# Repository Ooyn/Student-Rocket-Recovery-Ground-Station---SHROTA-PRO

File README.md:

# Student-Rocket-Recovery-Ground-Station---SHROTA-PRO
Shrota Pro is a custom-engineered, portable ground station PCB specifically designed to track and recover student-built rockets after touchdown. Acting as a specialized, relative GPS system, the handheld device receives critical telemetry data from the rocket and calculates its exact landing coordinates relative to the user's current position, making post-flight retrieval highly efficient.

At the heart of the system is an STM32 microcontroller responsible for real-time processing of incoming telemetry, parsing GPS data, managing sensor inputs, and driving the user interface. The board is powered by a 7.4V dual battery bus, utilizing step-down switching regulators to provide stable 5V and 3.3V rails. This robust power management ensures reliable operation of the MCU, sensitive RF equipment, and the onboard screen interface, allowing users to read relative distances and headings directly in the field. Standardized USB connectivity is also integrated for flashing firmware and serial debugging.

To accurately pinpoint positions, the board utilizes a multi-sensor navigation suite featuring an L89 GNSS module, a NEO-M8N GNSS module, and a BMM150 3-axis geomagnetic sensor that acts as a digital compass to determine the user's precise heading. For reliable long-range telemetry reception, the system incorporates a versatile radio block. It integrates RYLR998 and LLCC68 LoRa modules for robust, low-power communication links, alongside an RFD900x radio modem interface for extended range, ensuring the recovery team maintains a solid, line-of-sight connection to the downed rocket.

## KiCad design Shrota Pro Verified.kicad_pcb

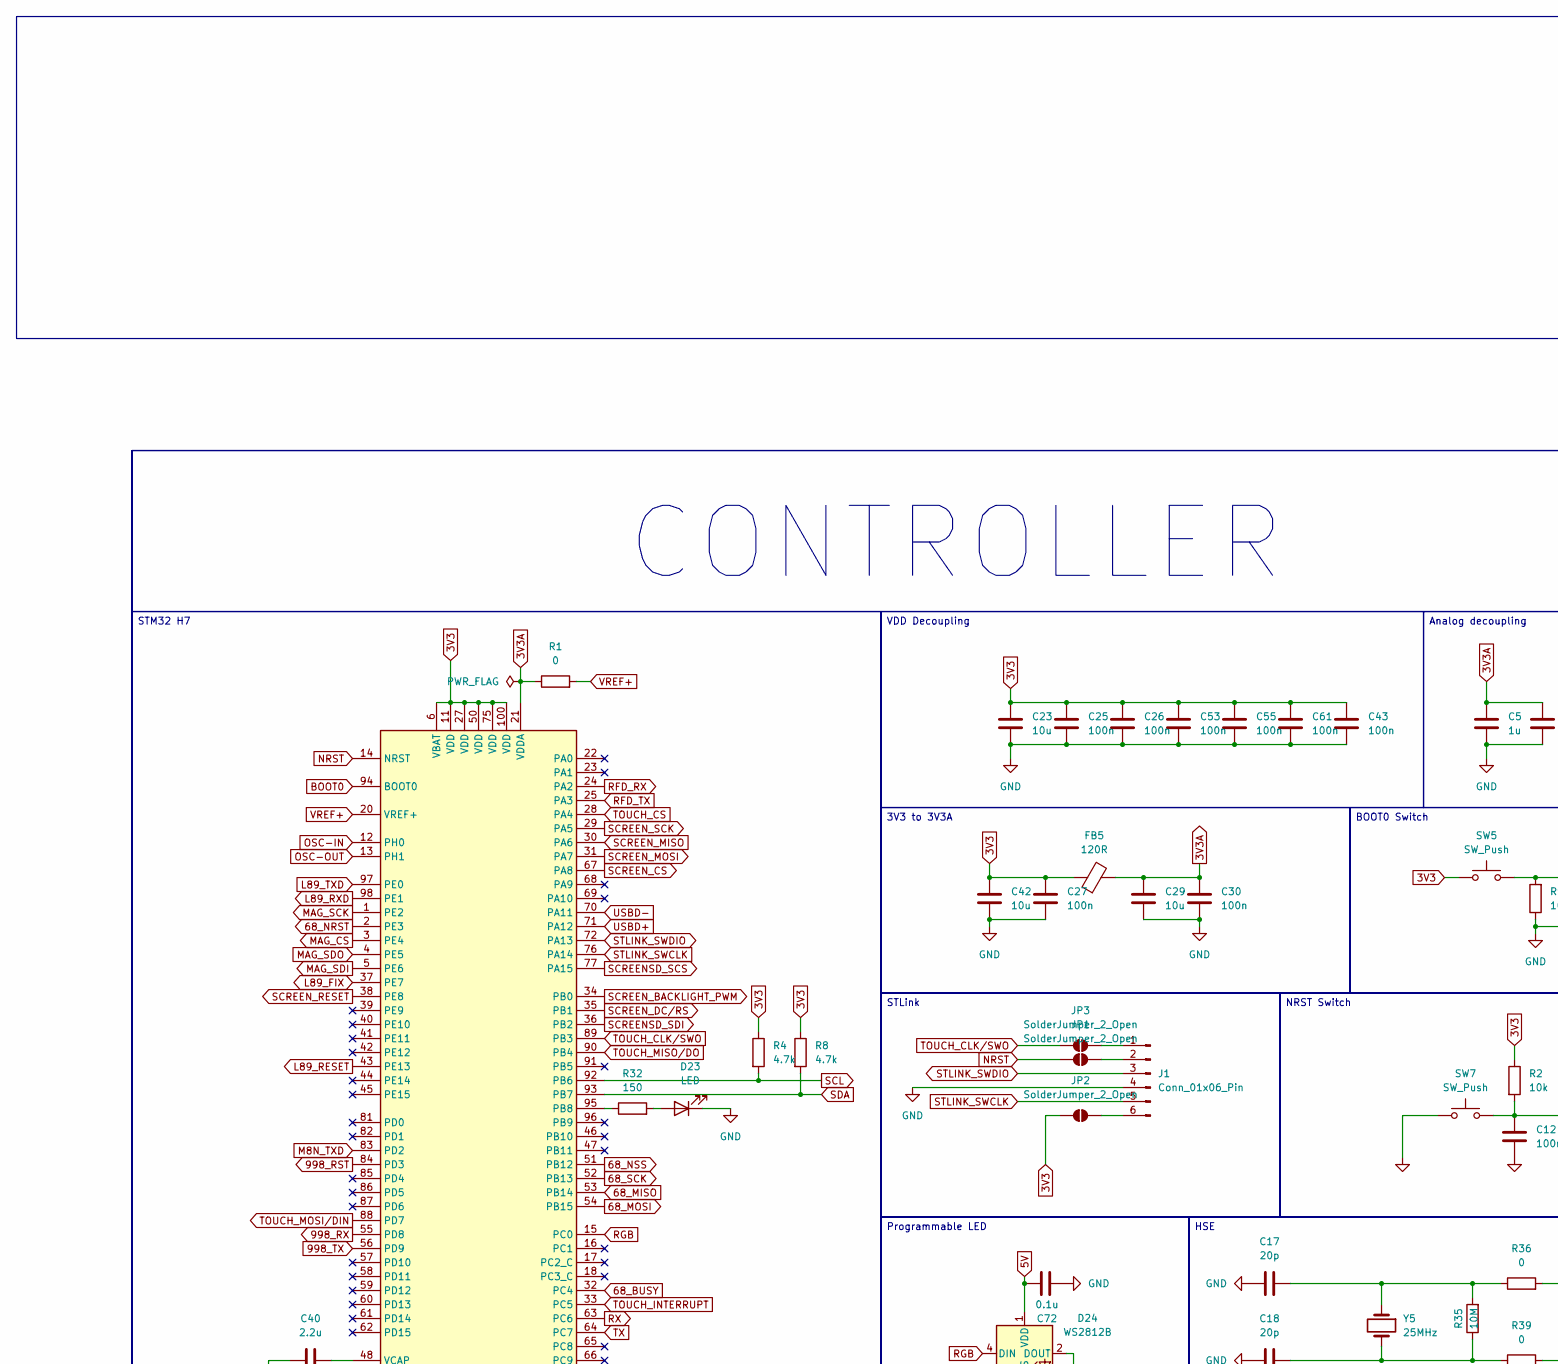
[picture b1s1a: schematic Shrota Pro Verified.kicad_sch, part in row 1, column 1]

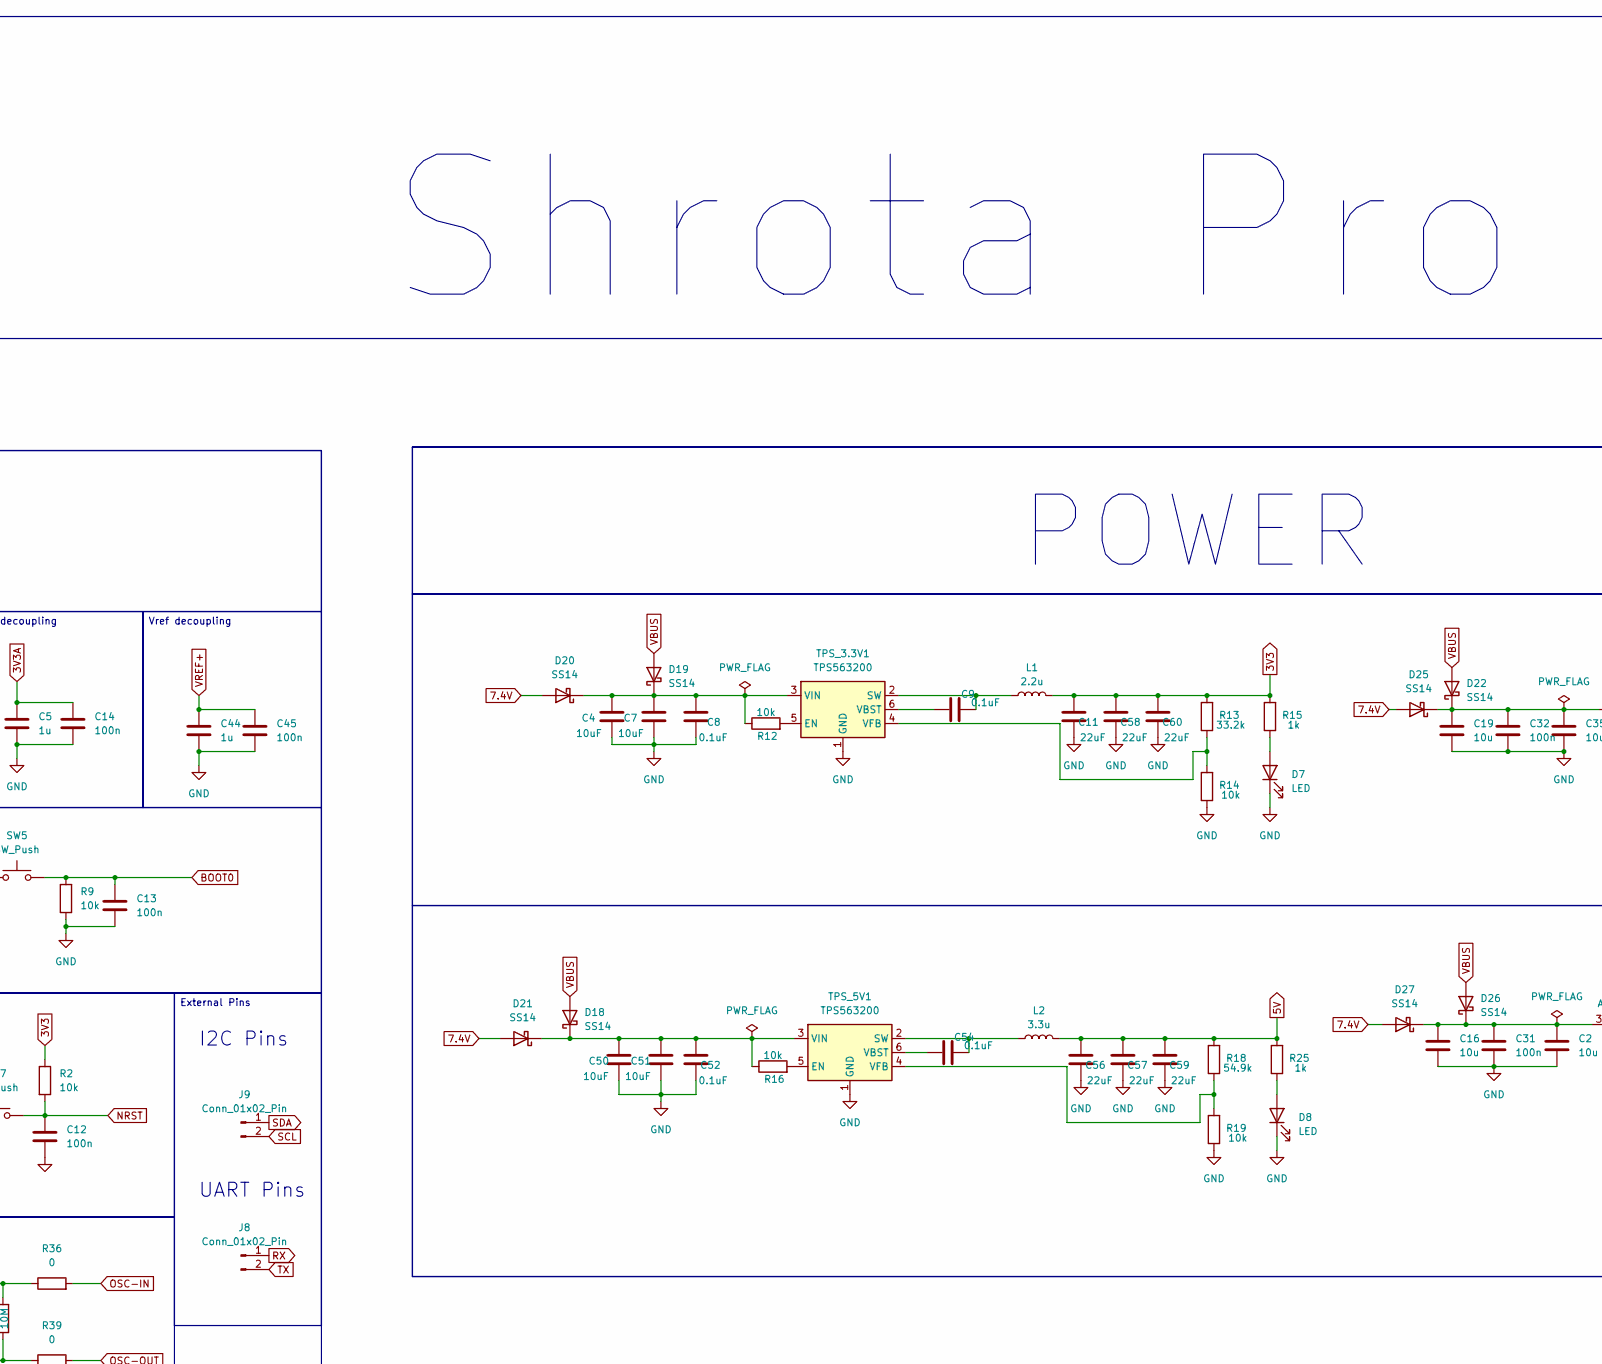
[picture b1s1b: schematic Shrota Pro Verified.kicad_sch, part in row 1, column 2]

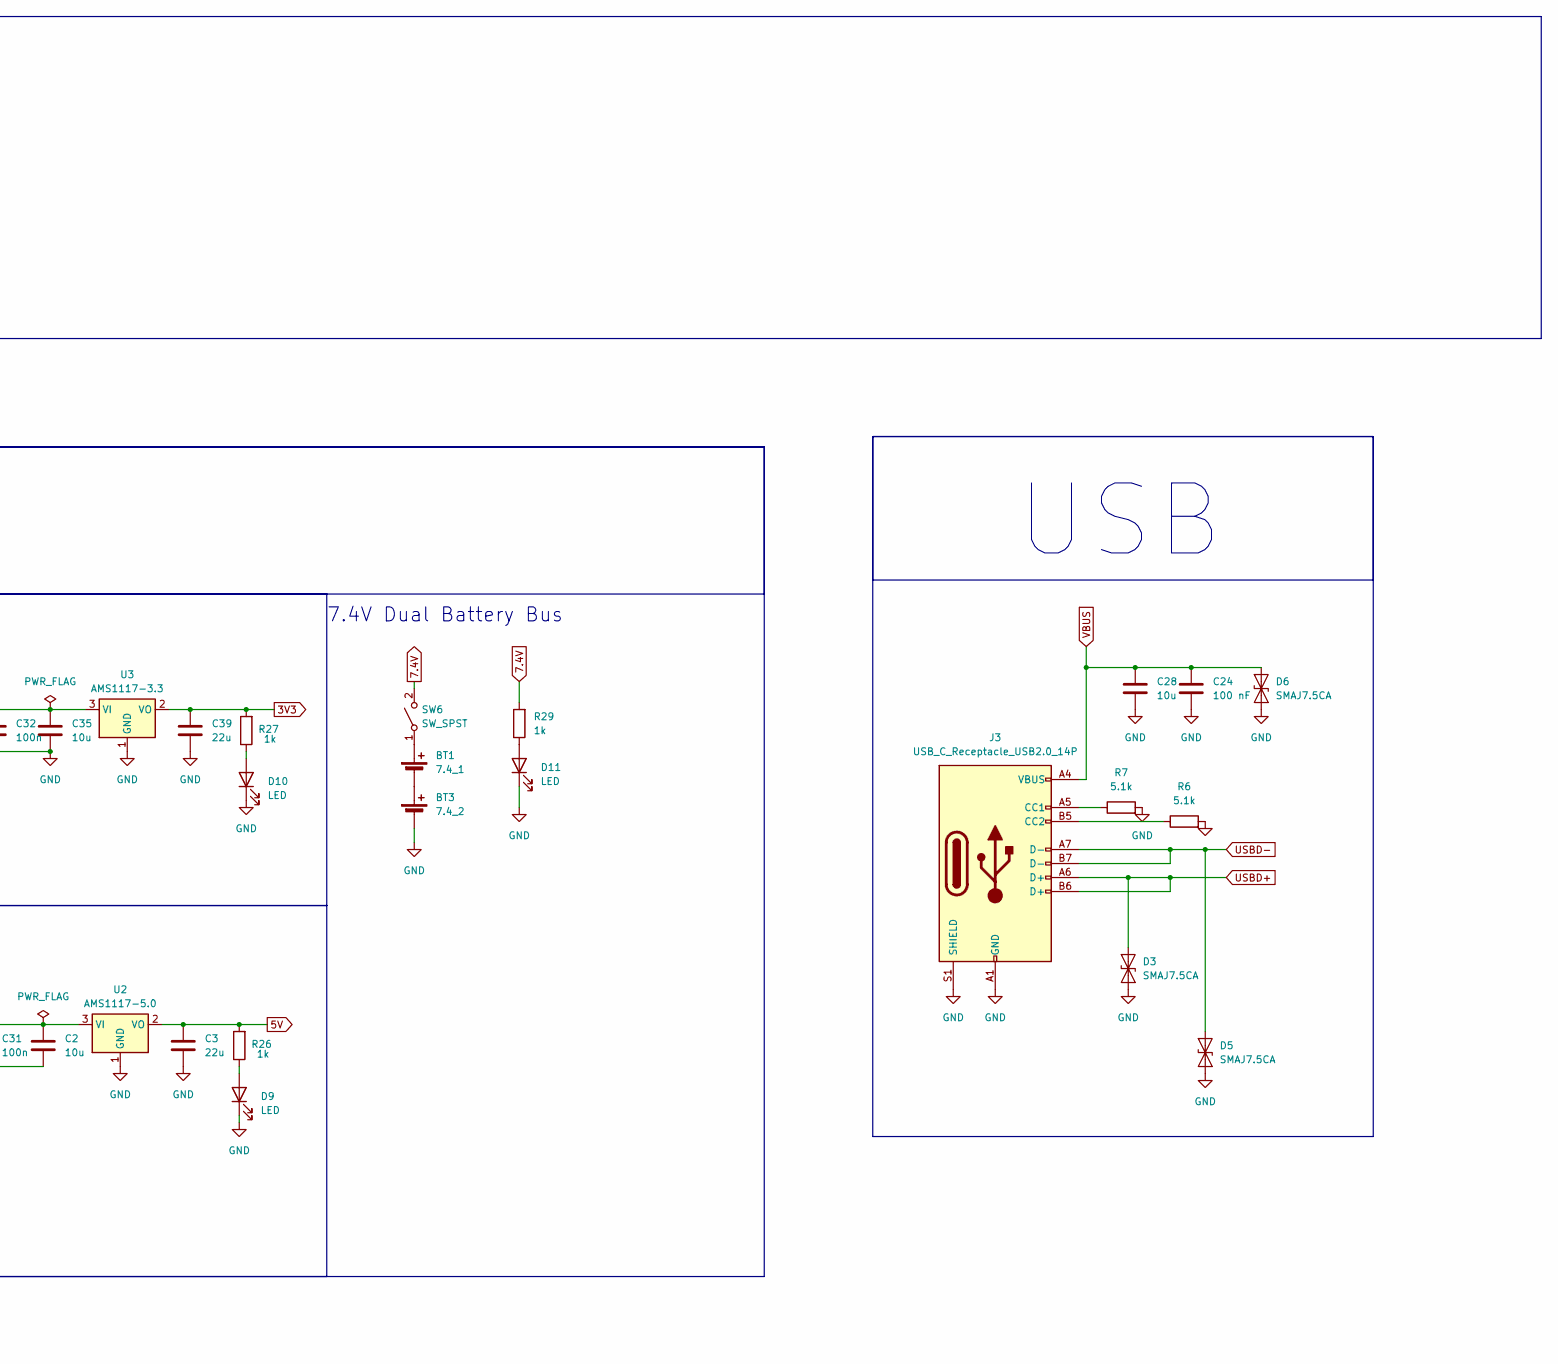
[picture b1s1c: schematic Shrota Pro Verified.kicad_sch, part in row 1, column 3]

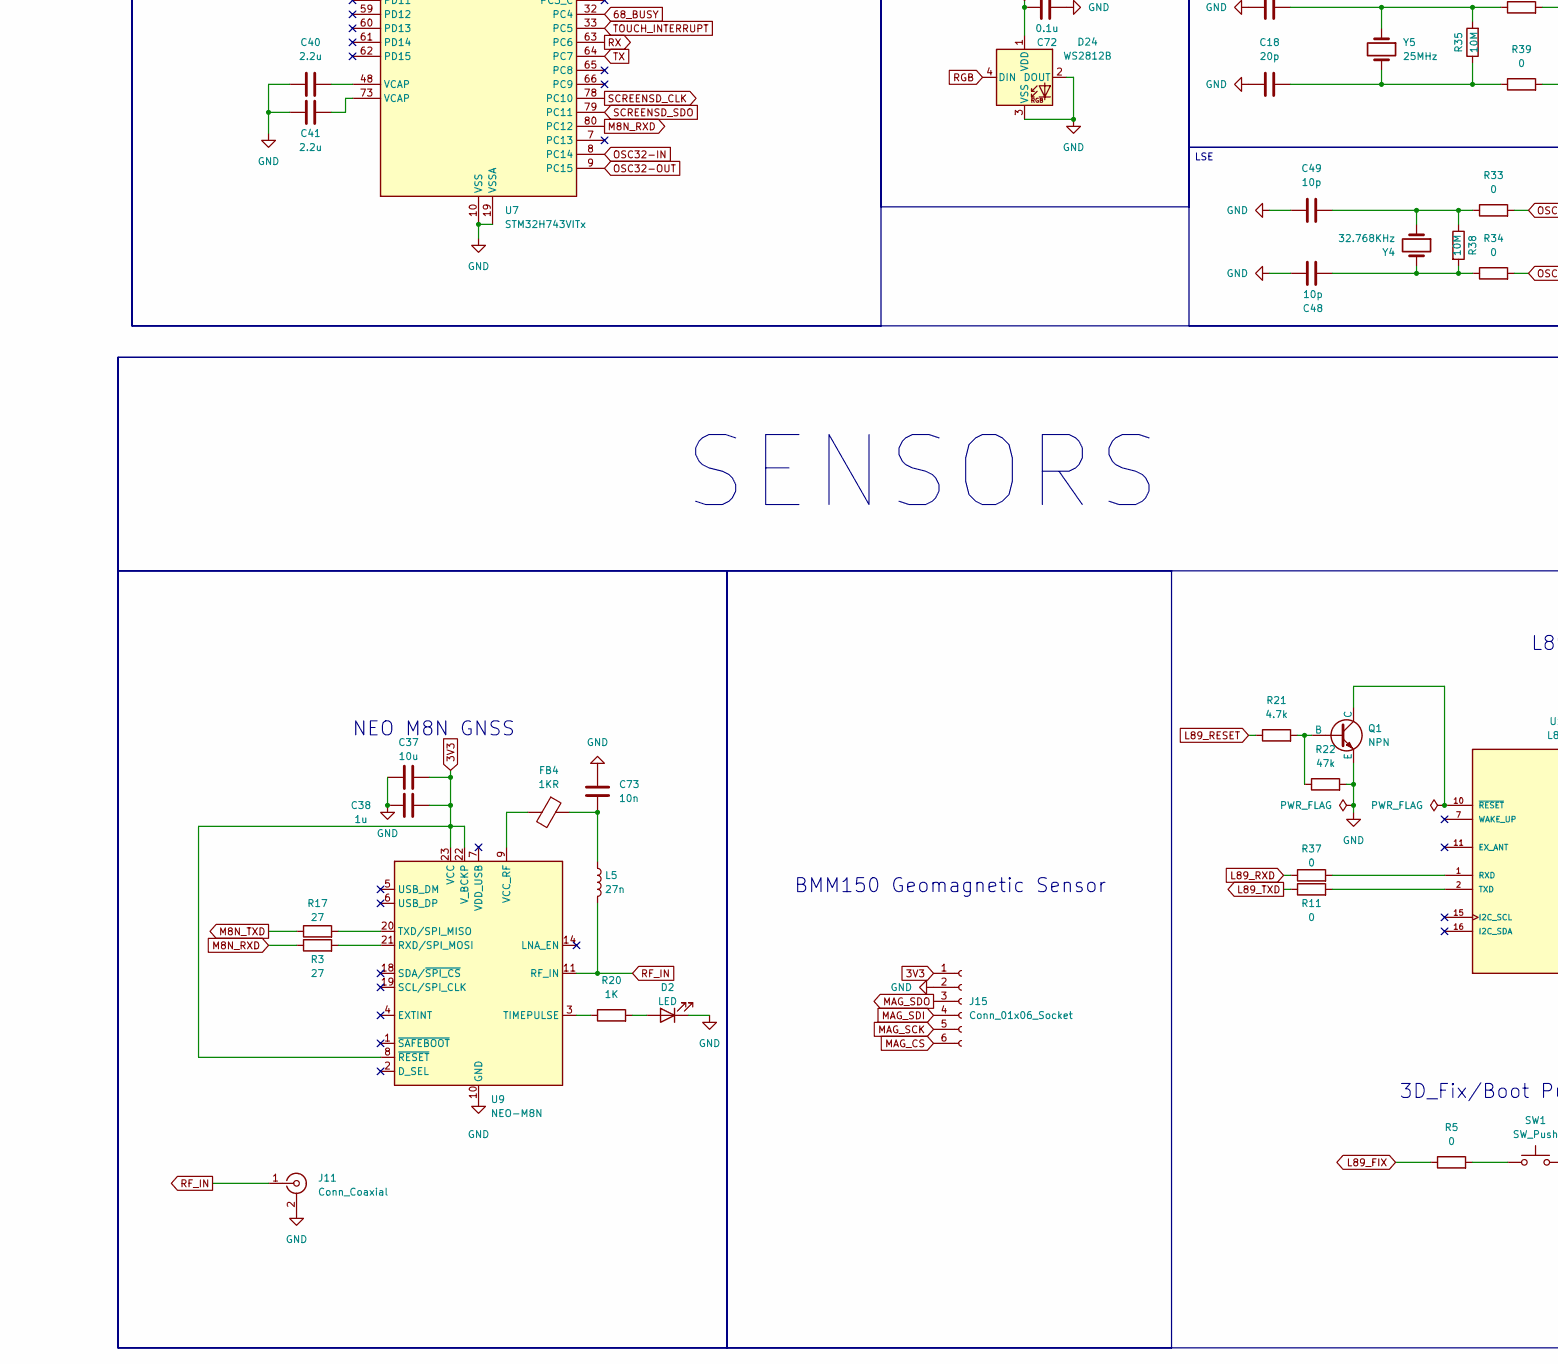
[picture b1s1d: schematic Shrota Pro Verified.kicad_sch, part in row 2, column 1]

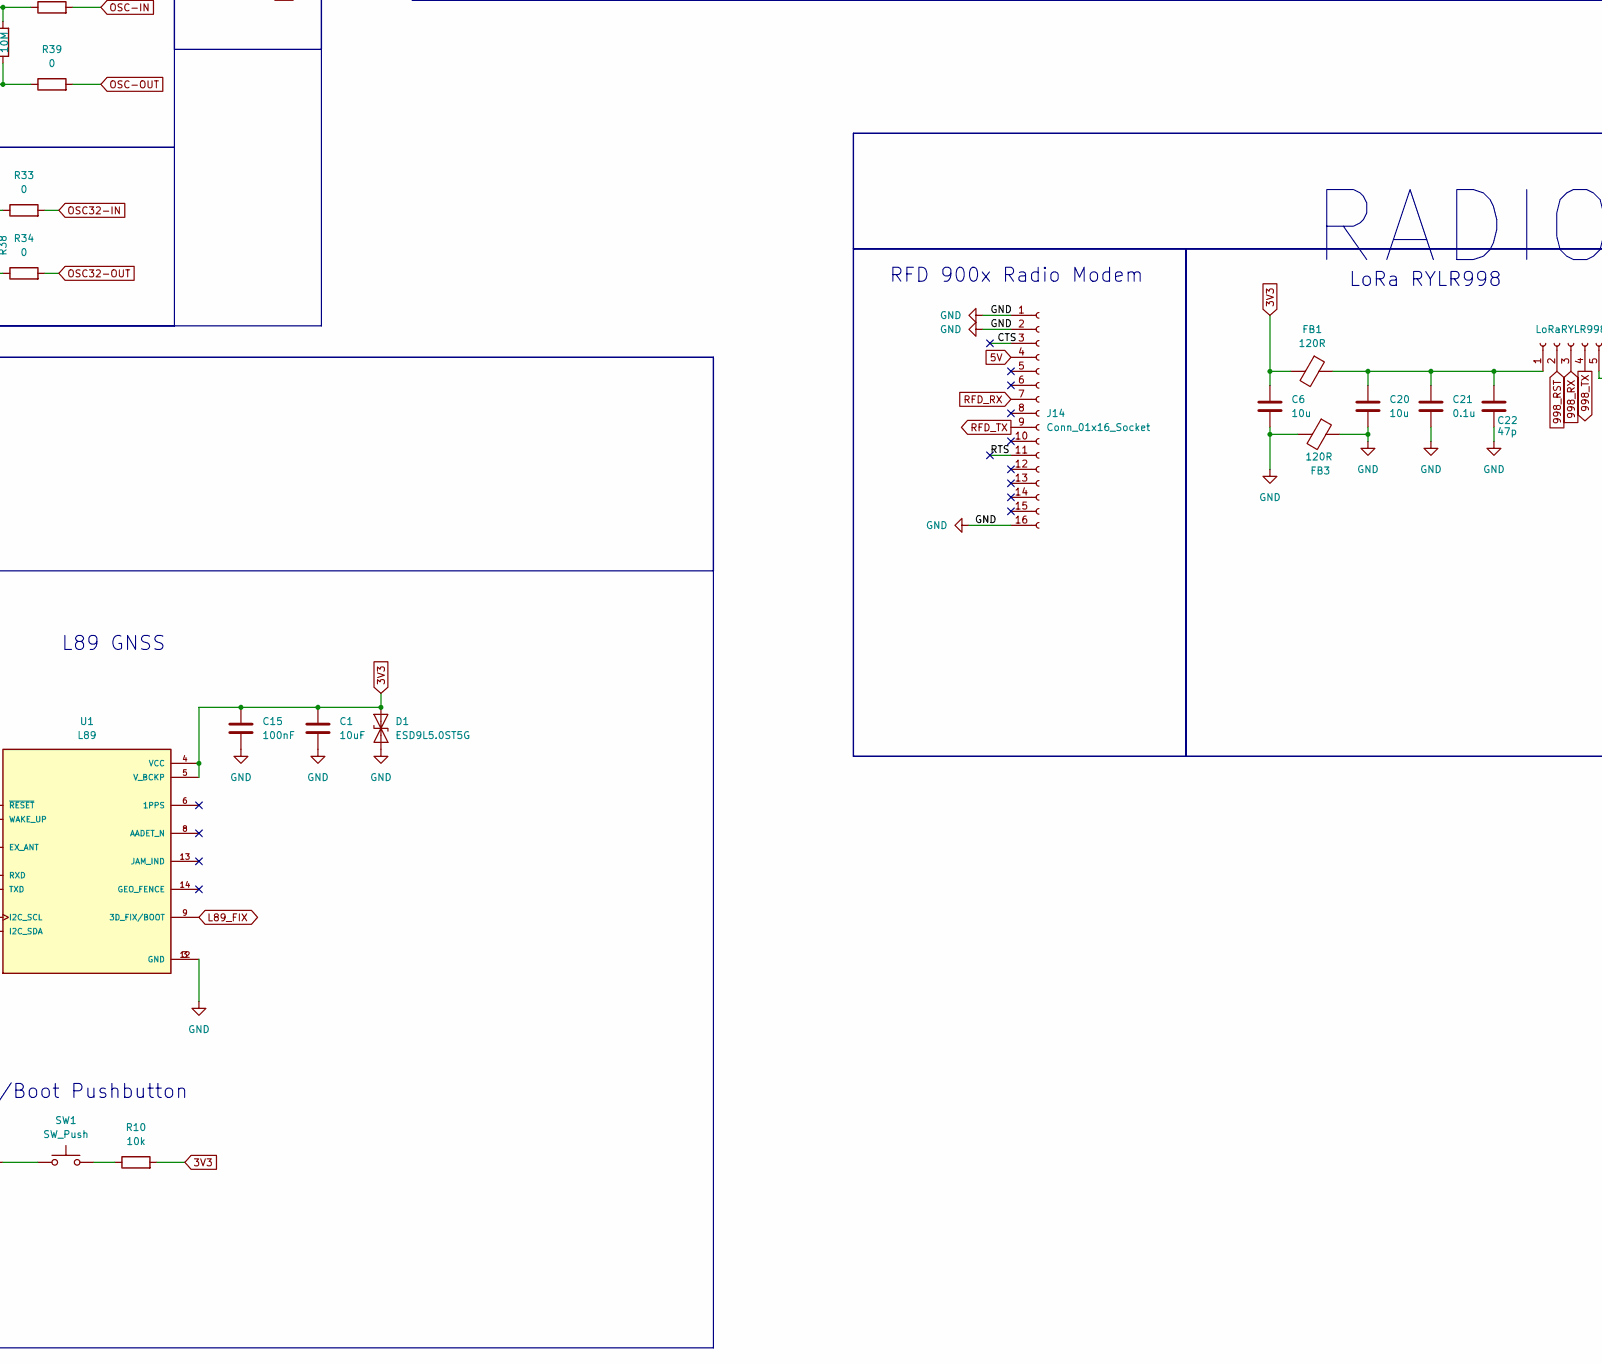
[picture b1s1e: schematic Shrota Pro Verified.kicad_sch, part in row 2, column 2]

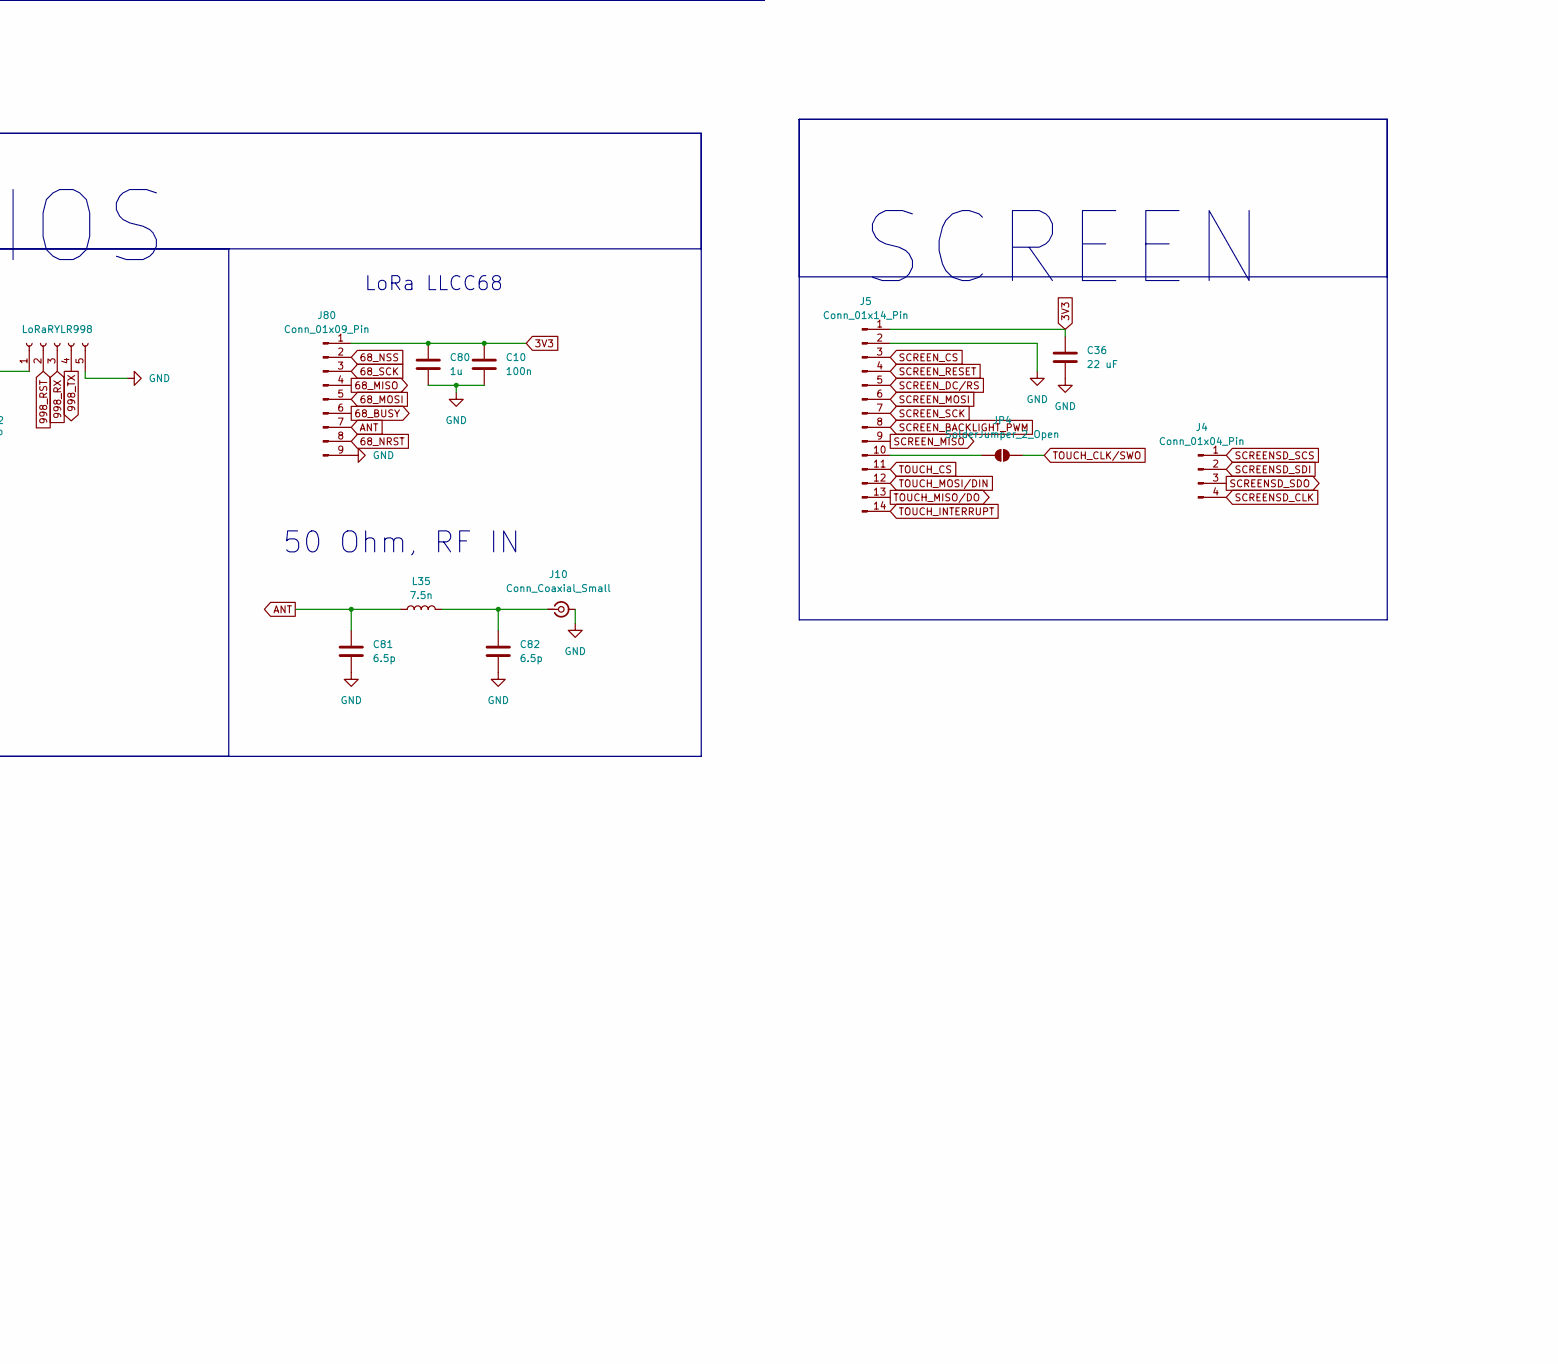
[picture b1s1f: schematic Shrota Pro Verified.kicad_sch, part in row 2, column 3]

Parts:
BT1: 7.4_1; BatteryHolder_Keystone_1042_1x18650
BT3: 7.4_2; BatteryHolder_Keystone_1042_1x18650
C1, C4, C7, C50, C51: 10uF; C_0603_1608Metric_Pad1.08x0.95mm_HandSolder
C2, C6, C16, C19, C20, C23, C28, C29, C35, C37, C42: 10u; C_0603_1608Metric_Pad1.08x0.95mm_HandSolder
C3, C39: 22u; C_1206_3216Metric_Pad1.33x1.80mm_HandSolder
C5, C38, C44, C80: 1u; C_0603_1608Metric_Pad1.08x0.95mm_HandSolder
C8, C9, C52, C54: 0.1uF; C_0603_1608Metric_Pad1.08x0.95mm_HandSolder
C10, C12, C13, C14, C25, C26, C27, C30, C31, C32, C43, C45, C53, C55, C61: 100n; C_0603_1608Metric_Pad1.08x0.95mm_HandSolder
C11, C56, C57, C58, C59, C60: 22uF; C_1206_3216Metric_Pad1.33x1.80mm_HandSolder
C15: 100nF; C_0603_1608Metric_Pad1.08x0.95mm_HandSolder
C17, C18: 20p; C_0603_1608Metric_Pad1.08x0.95mm_HandSolder
C21, C72: 0.1u; C_0603_1608Metric_Pad1.08x0.95mm_HandSolder
C22: 47p; C_0603_1608Metric_Pad1.08x0.95mm_HandSolder
C24: 100 nF; C_0603_1608Metric_Pad1.08x0.95mm_HandSolder
C36: 22 uF; C_0603_1608Metric_Pad1.08x0.95mm_HandSolder
C40, C41: 2.2u; C_0603_1608Metric_Pad1.08x0.95mm_HandSolder
C48, C49: 10p; C_0603_1608Metric_Pad1.08x0.95mm_HandSolder
C73: 10n; C_0603_1608Metric_Pad1.08x0.95mm_HandSolder
C81, C82: 6.5p; C_0603_1608Metric_Pad1.08x0.95mm_HandSolder
D1: ESD9L5.0ST5G; D_SOD-923
D2, D7, D8, D9, D10, D11, D23: LED; LED_0603_1608Metric_Pad1.05x0.95mm_HandSolder
D3, D5, D6: SMAJ7.5CA; D_SMA
D18, D19, D20, D21, D22, D25, D26, D27: SS14; DO-214AC
D24: WS2812B; LED_WS2812B_PLCC4_5.0x5.0mm_P3.2mm
FB1, FB3, FB5: 120R; L_0603_1608Metric_Pad1.05x0.95mm_HandSolder
FB4: 1KR; L_0603_1608Metric_Pad1.05x0.95mm_HandSolder
J1: Conn_01x06_Pin; PinHeader_1x06_P2.54mm_Vertical
J2: LoRaRYLR998; PinSocket_1x05_P2.54mm_Vertical
J3: USB_C_Receptacle_USB2.0_14P; USB_C_Receptacle_GCT_USB4105-xx-A_16P_TopMnt_Horizontal
J4: Conn_01x04_Pin; PinSocket_1x04_P2.54mm_Vertical
J5: Conn_01x14_Pin; PinSocket_1x14_P2.54mm_Vertical
J8, J9: Conn_01x02_Pin; PinSocket_1x02_P2.54mm_Vertical
J10: Conn_Coaxial_Small; SMA_Amphenol_901-143_Horizontal
J11: Conn_Coaxial; U.FL_Hirose_U.FL-R-SMT-1_Vertical
J14: Conn_01x16_Socket; PinSocket_2x08_P2.54mm_Vertical
J15: Conn_01x06_Socket; PinSocket_1x06_P2.54mm_Vertical
J80: Conn_01x09_Pin; PinSocket_1x09_P2.54mm_Vertical
JP1, JP2, JP3, JP4: SolderJumper_2_Open; SolderJumper-2_P1.3mm_Open_Pad1.0x1.5mm
L1: 2.2u; L_Sunlord_SWPA6045S
L2: 3.3u; L_Sunlord_SWPA8040S
L5: 27n; L_0603_1608Metric_Pad1.05x0.95mm_HandSolder
L35: 7.5n; L_0603_1608Metric_Pad1.05x0.95mm_HandSolder
Q1: NPN; SOT-23
R1, R5, R11, R33, R34, R36, R37, R39: 0; R_0603_1608Metric_Pad0.98x0.95mm_HandSolder
R2, R9, R10, R12, R14, R16, R19: 10k; R_0603_1608Metric_Pad0.98x0.95mm_HandSolder
R3, R17: 27; R_0603_1608Metric_Pad0.98x0.95mm_HandSolder
R4, R8, R21: 4.7k; R_0603_1608Metric_Pad0.98x0.95mm_HandSolder
R6, R7: 5.1k; R_0603_1608Metric_Pad0.98x0.95mm_HandSolder
R13: 33.2k; R_0603_1608Metric_Pad0.98x0.95mm_HandSolder
R15, R25, R26, R27, R29: 1k; R_0603_1608Metric_Pad0.98x0.95mm_HandSolder
R18: 54.9k; R_0603_1608Metric_Pad0.98x0.95mm_HandSolder
R20: 1K; R_0603_1608Metric_Pad0.98x0.95mm_HandSolder
R22: 47k; R_0603_1608Metric_Pad0.98x0.95mm_HandSolder
R32: 150; R_0603_1608Metric_Pad0.98x0.95mm_HandSolder
R35, R38: 10M; R_0603_1608Metric
SW1: SW_Push; SW_PUSH_6mm
SW5, SW7: SW_Push; SW_Push_1P1T_NO_CK_KMR2
SW6: SW_SPST; SW_DIP_SPSTx01_Slide_9.78x4.72mm_W8.61mm_P2.54mm
TPS_3.3V1, TPS_5V1: TPS563200; SOT-23-6
U1: L89; XCVR_L89; PARTREV 1.1
U2: AMS1117-5.0; SOT-223-3_TabPin2
U3: AMS1117-3.3; SOT-223-3_TabPin2
U7: STM32H743VITx; LQFP-100_14x14mm_P0.5mm
U9: NEO-M8N; ublox_NEO
Y4: 32.768KHz; XTAL_ABS07AIG-32.768KHZ-1-T
Y5: 25MHz; XTAL_ABLS-25.000MHZ-B2F-T

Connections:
3V3: C1.1, C6.1, C10.1, C11.2, C15.1, C23.1, C25.1, C26.1, C27.1, C36.1, C37.1, C38.1, C39.1, C42.1, C43.1, C53.1, C55.1, C58.2, C60.2, C61.1, C80.1, D1.2 (A2), FB1.2, FB5.1, J5.1, J15.1, J80.1, JP2.1 (A), L1.2, R2.1, R4.1, R8.1, R10.2, R13.2, R15.2, R27.2, SW5.1, U1.4 (VCC), U1.5 (V_BCKP), U3.2 (VO), U7.6 (VBAT), U7.11 (VDD), U7.27 (VDD), U7.50 (VDD), U7.75 (VDD), U7.100 (VDD), U9.8 (~RESET), U9.22 (V_BCKP), U9.23 (VCC)
3V3A: C5.1, C14.1, C29.1, C30.1, FB5.2, R1.1, U7.21 (VDDA)
5V: C3.1, C56.2, C57.2, C59.2, C72.2, D24.1 (VDD), J14.4, L2.2, R18.2, R25.2, R26.2, U2.2 (VO)
7.4V: D20.2 (A), D21.2 (A), D25.2 (A), D27.2 (A), R29.2, SW6.2 (B)
68_BUSY: J80.6, U7.32 (PC4)
68_MISO: J80.4, U7.53 (PB14)
68_MOSI: J80.5, U7.54 (PB15)
68_NRST: J80.8, U7.2 (PE3)
68_NSS: J80.2, U7.51 (PB12)
68_SCK: J80.3, U7.52 (PB13)
998_RST: J2.2, U7.84 (PD3)
998_RX: J2.3, U7.55 (PD8)
998_TX: J2.4, U7.56 (PD9)
/CTS: J14.3
/RTS: J14.11
ANT: C81.1, J80.7, L35.1
BOOT0: C13.1, R9.2, SW5.2, U7.94 (BOOT0)
GND: BT3.2 (-), C1.2, C2.2, C3.2, C4.1, C5.2, C6.2, C7.1, C8.1, C10.2, C11.1, C12.2, C13.2, C14.2, C15.2, C16.2, C17.1, C18.1, C19.2, C20.2, C21.2, C22.2, C23.2, C24.2, C25.2, C26.2, C27.2, C28.2, C29.2, C30.2, C31.2, C32.2, C35.2, C36.2, C37.2, C38.2, C39.2, C40.1, C41.2, C42.2, C43.2, C44.2, C45.2, C48.2, C49.2, C50.1, C51.1, C52.1, C53.2, C55.2, C56.1, C57.1, C58.1, C59.1, C60.1, C61.2, C72.1, C73.1, C80.2, C81.2, C82.2, D1.1 (A1), D2.1 (K), D3.1 (A1), D5.1 (A1), D6.1 (A1), D7.1 (K), D8.1 (K), D9.1 (K), D10.1 (K), D11.1 (K), D23.1 (K), D24.2 (DOUT), D24.3 (VSS), FB3.1, FB3.2, J1.4, J2.5, J3.A1 (GND), J3.A12 (GND), J3.B1 (GND), J3.B12 (GND), J3.S1 (SHIELD), J5.2, J10.2 (Ext), J11.2 (Ext), J14.1, J14.2, J14.16, J15.2, J80.9, Q1.3 (E), R6.2, R7.2, R9.1, R14.1, R19.1, R22.2, SW7.1, TPS_3.3V1.1 (GND), TPS_5V1.1 (GND), U1.3 (GND), U1.12 (GND), U2.1 (GND), U3.1 (GND), U7.10 (VSS), U7.19 (VSSA), U7.26 (VSS), U7.49 (VSS), U7.74 (VSS), U7.99 (VSS), U9.10 (GND), U9.12 (GND), U9.13 (GND), U9.24 (GND)
L89_FIX: R5.1, U1.9 (3D_FIX/BOOT), U7.37 (PE7)
L89_RESET: R21.1, U7.43 (PE13)
L89_RXD: R37.1, U7.98 (PE1)
L89_TXD: R11.1, U7.97 (PE0)
M8N_RXD: R3.1, U7.80 (PC12)
M8N_TXD: R17.1, U7.83 (PD2)
MAG_CS: J15.6, U7.3 (PE4)
MAG_SCK: J15.5, U7.1 (PE2)
MAG_SDI: J15.4, U7.5 (PE6)
MAG_SDO: J15.3, U7.4 (PE5)
NRST: C12.1, JP1.1 (A), R2.2, SW7.2, U7.14 (NRST)
unnamed: BT1.1 (+), SW6.1 (A)
unnamed: BT1.2 (-), BT3.1 (+)
unnamed: C17.2, R35.2, R36.1, Y5.1
unnamed: C18.2, R35.1, R39.1, Y5.2
unnamed: C40.2, U7.48 (VCAP)
unnamed: C41.1, U7.73 (VCAP)
unnamed: C48.1, R34.1, R38.2, Y4.2
unnamed: C49.1, R33.1, R38.1, Y4.1
unnamed: C73.2, FB4.1, L5.1
unnamed: D2.2 (A), R20.2
unnamed: D7.2 (A), R15.1
unnamed: D8.2 (A), R25.1
unnamed: D9.2 (A), R26.1
unnamed: D10.2 (A), R27.1
unnamed: D11.2 (A), R29.1
unnamed: C50.2, C51.2, C52.2, D18.1 (K), D21.1 (K), R16.1, TPS_5V1.3 (VIN)
unnamed: C4.2, C7.2, C8.2, D19.1 (K), D20.1 (K), R12.1, TPS_3.3V1.3 (VIN)
unnamed: C19.1, C32.1, C35.1, D22.1 (K), D25.1 (K), U3.3 (VI)
unnamed: D23.2 (A), R32.2
unnamed: C2.1, C16.1, C31.1, D26.1 (K), D27.1 (K), U2.3 (VI)
unnamed: J1.1, JP3.2 (B)
unnamed: J1.2, JP1.2 (B)
unnamed: J1.6, JP2.2 (B)
unnamed: C20.1, C21.1, C22.1, FB1.1, J2.1
unnamed: J3.A5 (CC1), R7.1
unnamed: J3.B5 (CC2), R6.1
unnamed: J5.10, JP4.1 (A)
unnamed: C82.1, J10.1 (In), L35.2
unnamed: Q1.2 (B), R21.2, R22.1
unnamed: Q1.1 (C), U1.10 (~RESET)
unnamed: R5.2, SW1.1
unnamed: R10.1, SW1.2
unnamed: R12.2, TPS_3.3V1.5 (EN)
unnamed: C9.1, L1.1, TPS_3.3V1.2 (SW)
unnamed: C9.2, TPS_3.3V1.6 (VBST)
unnamed: R13.1, R14.2, TPS_3.3V1.4 (VFB)
unnamed: R16.2, TPS_5V1.5 (EN)
unnamed: C54.1, L2.1, TPS_5V1.2 (SW)
unnamed: C54.2, TPS_5V1.6 (VBST)
unnamed: R18.1, R19.2, TPS_5V1.4 (VFB)
unnamed: R37.2, U1.1 (RXD)
unnamed: R11.2, U1.2 (TXD)
unnamed: R32.1, U7.95 (PB8)
unnamed: R3.2, U9.21 (RXD/SPI_MOSI)
unnamed: R20.1, U9.3 (TIMEPULSE)
unnamed: R17.2, U9.20 (TXD/SPI_MISO)
unnamed: FB4.2, U9.9 (VCC_RF)
OSC32-IN: R33.2, U7.8 (PC14)
OSC32-OUT: R34.2, U7.9 (PC15)
OSC-IN: R36.2, U7.12 (PH0)
OSC-OUT: R39.2, U7.13 (PH1)
RFD_RX: J14.7, U7.24 (PA2)
RFD_TX: J14.9, U7.25 (PA3)
RF_IN: J11.1 (In), L5.2, U9.11 (RF_IN)
RGB: D24.4 (DIN), U7.15 (PC0)
RX: J8.1, U7.63 (PC6)
SCL: J9.2, R4.2, U7.92 (PB6)
SCREENSD_CLK: J4.4, U7.78 (PC10)
SCREENSD_SCS: J4.1, U7.77 (PA15)
SCREENSD_SDI: J4.2, U7.36 (PB2)
SCREENSD_SDO: J4.3, U7.79 (PC11)
SCREEN_BACKLIGHT_PWM: J5.8, U7.34 (PB0)
SCREEN_CS: J5.3, U7.67 (PA8)
SCREEN_DC/RS: J5.5, U7.35 (PB1)
SCREEN_MISO: J5.9, U7.30 (PA6)
SCREEN_MOSI: J5.6, U7.31 (PA7)
SCREEN_RESET: J5.4, U7.38 (PE8)
SCREEN_SCK: J5.7, U7.29 (PA5)
SDA: J9.1, R8.2, U7.93 (PB7)
STLINK_SWCLK: J1.5, U7.76 (PA14)
STLINK_SWDIO: J1.3, U7.72 (PA13)
TOUCH_CLK/SWO: JP3.1 (A), JP4.2 (B), U7.89 (PB3)
TOUCH_CS: J5.11, U7.28 (PA4)
TOUCH_INTERRUPT: J5.14, U7.33 (PC5)
TOUCH_MISO/DO: J5.13, U7.90 (PB4)
TOUCH_MOSI/DIN: J5.12, U7.88 (PD7)
TX: J8.2, U7.64 (PC7)
USBD+: D3.2 (A2), J3.A6 (D+), J3.B6 (D+), U7.71 (PA12)
USBD-: D5.2 (A2), J3.A7 (D-), J3.B7 (D-), U7.70 (PA11)
VBUS: C24.1, C28.1, D6.2 (A2), D18.2 (A), D19.2 (A), D22.2 (A), D26.2 (A), J3.A4 (VBUS), J3.A9 (VBUS), J3.B4 (VBUS), J3.B9 (VBUS)
VREF+: C44.1, C45.1, R1.2, U7.20 (VREF+)

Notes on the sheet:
BMM150 Geomagnetic Sensor
LoRa LLCC68
L89 GNSS
USB
SCREEN
UART Pins
NEO M8N GNSS
50 Ohm, RF IN
LoRa RYLR998
3D_Fix/Boot Pushbutton
I2C Pins
RFD 900x Radio Modem
RADIOS
POWER
Shrota Pro
CONTROLLER
SENSORS
7.4V Dual Battery Bus
BOOT0 Switch
STM32 H7
NRST Switch
STLink
HSE
Programmable LED
VDD Decoupling
External Pins
Vref decoupling
3V3 to 3V3A
LSE
Analog decoupling

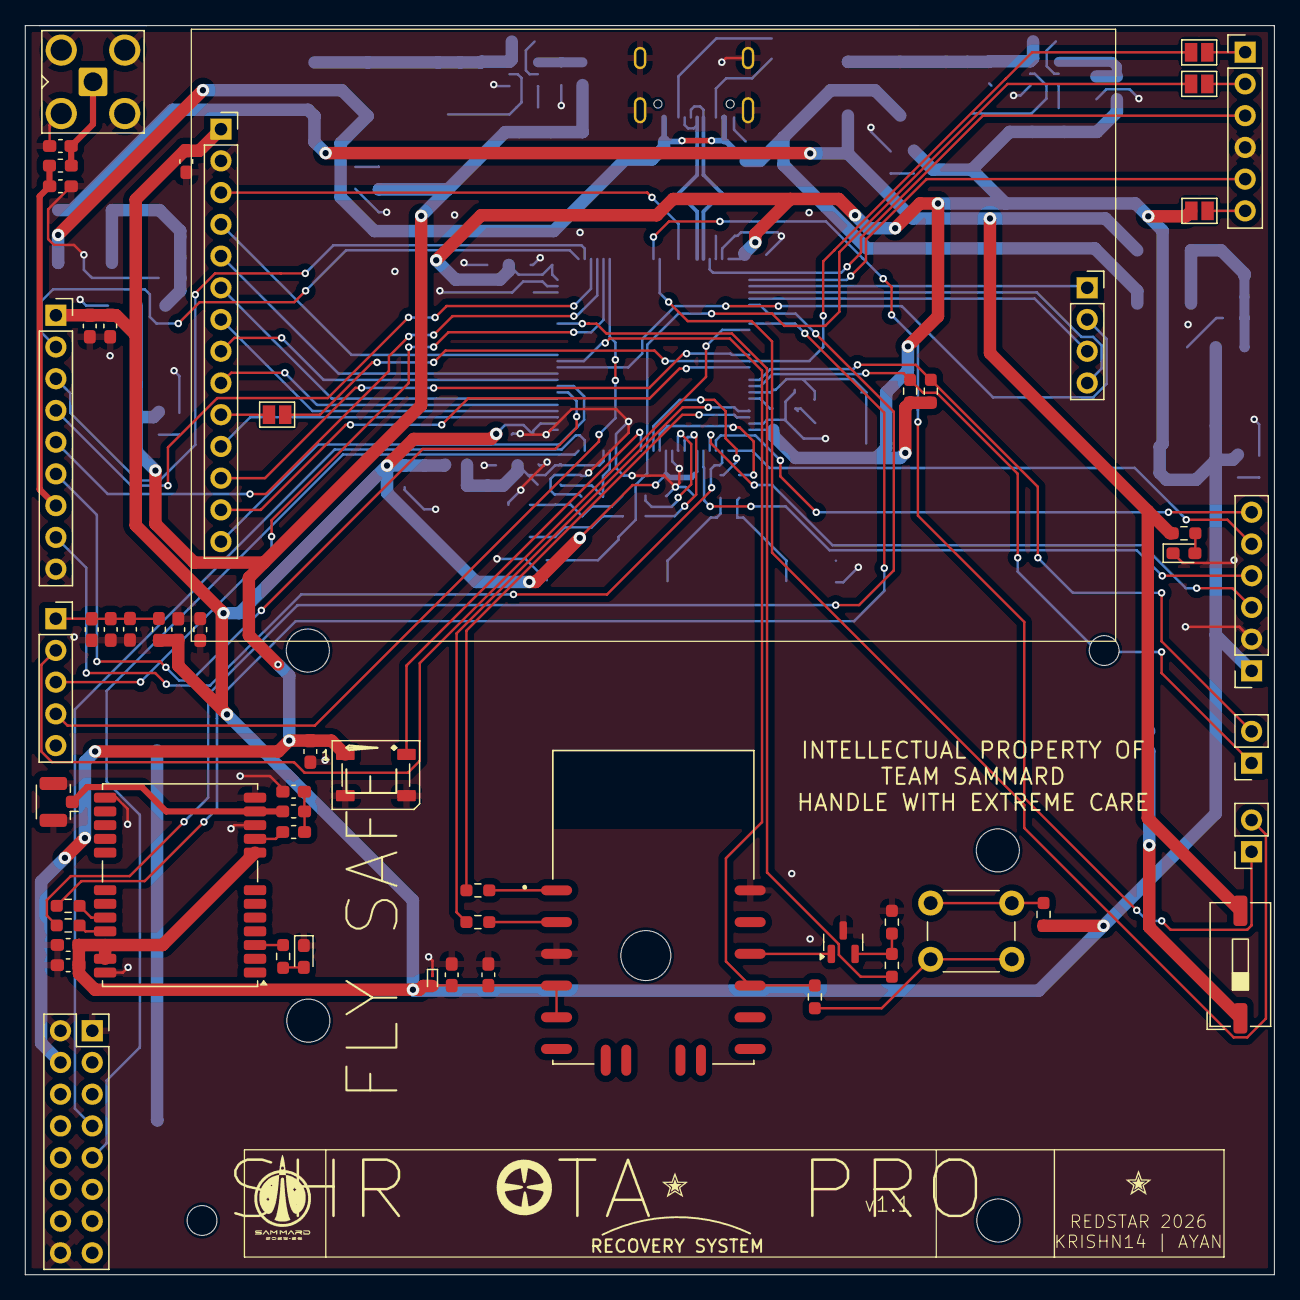
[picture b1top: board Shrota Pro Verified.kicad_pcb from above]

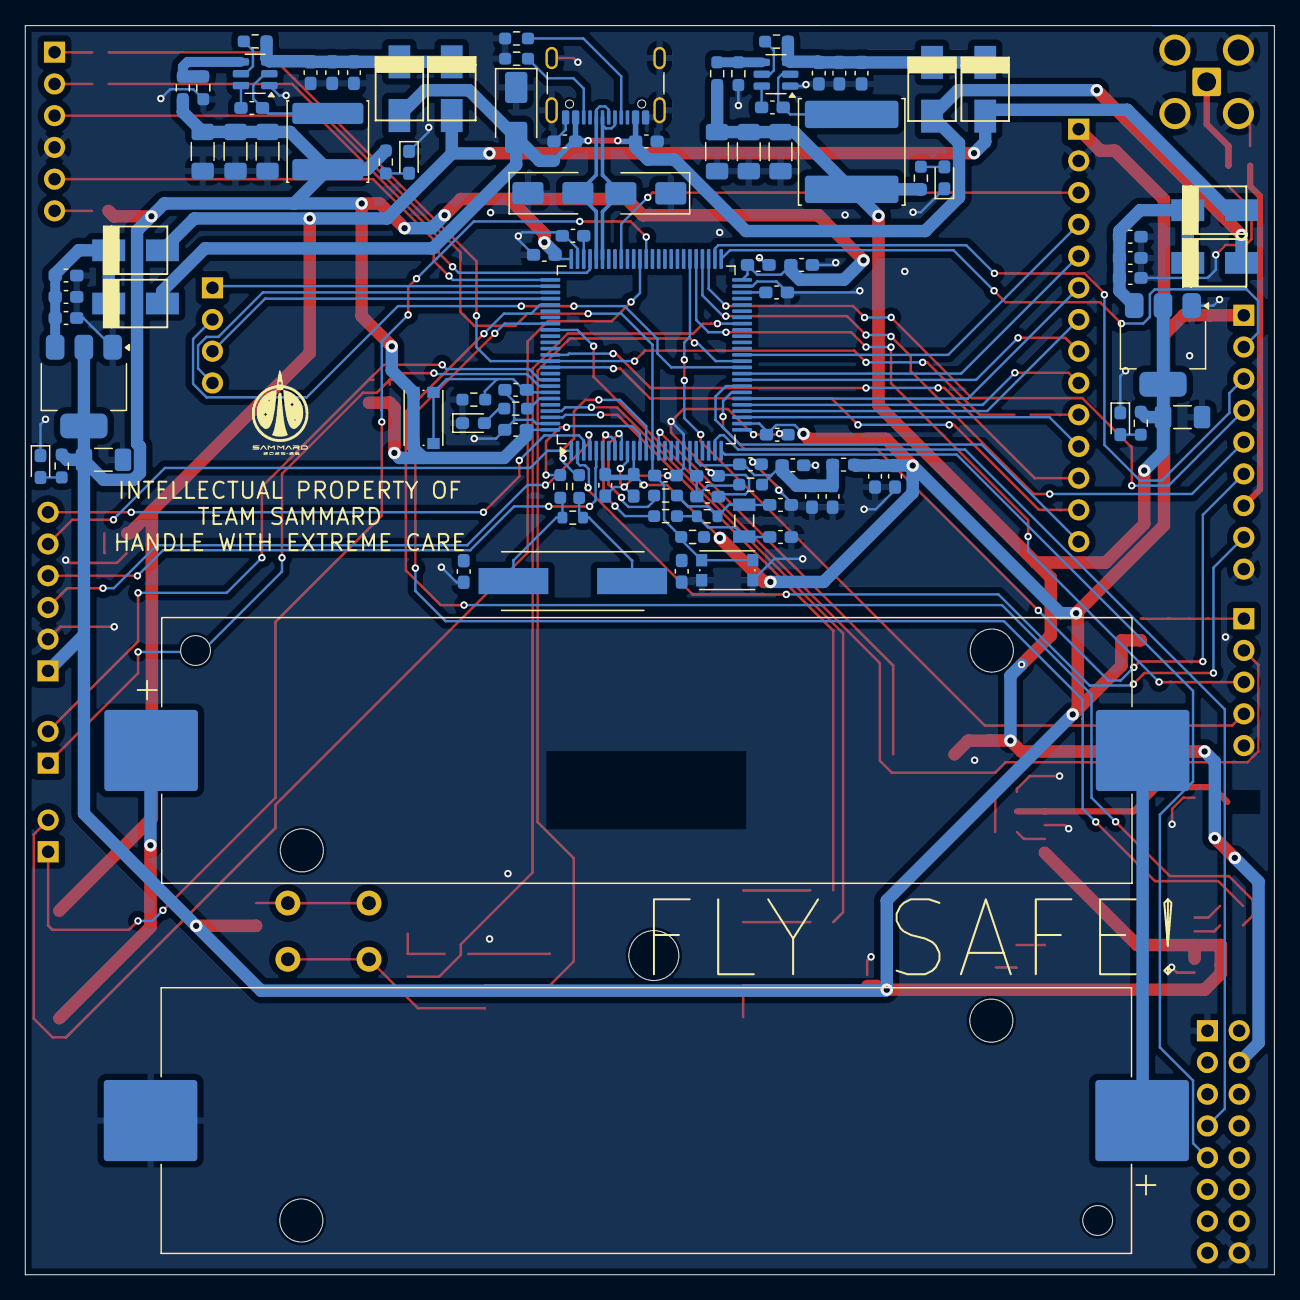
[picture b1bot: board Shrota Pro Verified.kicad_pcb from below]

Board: 2 copper layers, 100.0 x 100.0 mm, 156 parts (100 on the bottom side), 108 nets.

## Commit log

2026-03-11 Create LICENSE
